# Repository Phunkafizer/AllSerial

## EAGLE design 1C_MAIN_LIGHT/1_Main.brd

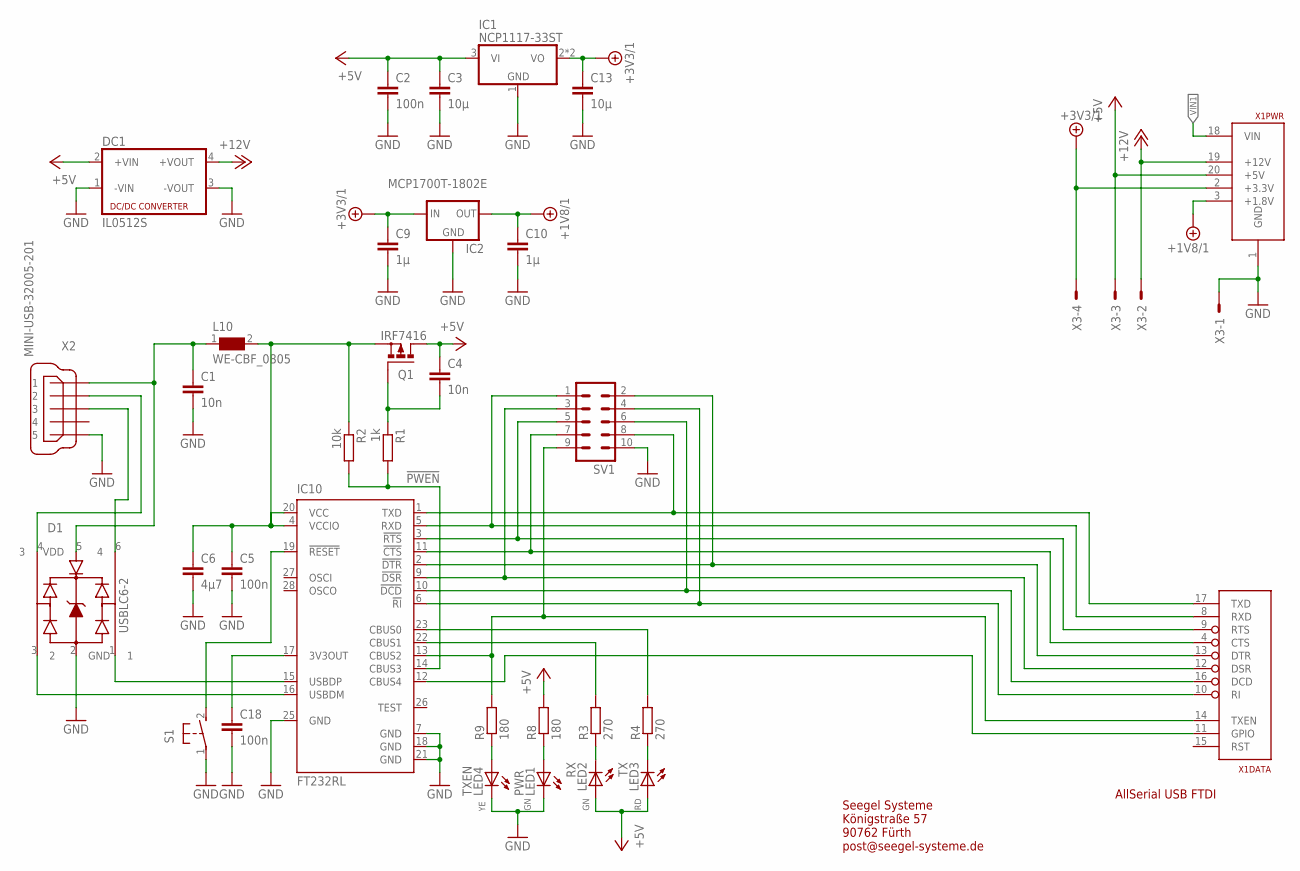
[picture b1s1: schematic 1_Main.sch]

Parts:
C1, C4: 10n; C0805
C2, C5, C18: 100n; C0805
C3, C13: 10µ; C0805
C6: 4µ7; C0805
C9, C10: 1µ; C0805
D1: USBLC6-2; WE-TVS_SOT23-6L
DC1: IL0512S; NME
IC1: NCP1117-33ST; SOT223
IC2: MCP1700T-1802E; SOT23
IC10: FT232RL; SSOP28
L10: WE-CBF_0805; 0805
LED1: PWR; CHIPLED_0603
LED2: RX; CHIPLED_0603
LED3: TX; CHIPLED_0603
LED4: TXEN; CHIPLED_0603
Q1: IRF7416; SO-08
R1: 1k; R0805
R2: 10k; R0805
R3, R4: 270; R0805
R8, R9: 180; R0805
S1: 31-XX; B3F-31XX
SV1: ML10
X1: ALLSERIALMASTERMM; MAIN-THT
X2: MINI-USB-32005-201; 32005-201
X3: AKL18X-04W; AKL182-04

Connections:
!PWEN: IC10.14 (CBUS3), R1.2, R2.2
+1V8/1: C10.1, IC2.2 (OUT), X1.3 (+1.8V)
+3V3/1: C9.1, C13.1, IC1.2 (VO), IC1.4 (VO), IC2.3 (IN), X1.2 (+3.3V), X3.P$4
+5V: C2.1, C3.1, C4.1, DC1.2 (+VIN), IC1.3 (VI), LED2.A, LED3.A, Q1.5 (D), Q1.6 (D), Q1.7 (D), Q1.8 (D), R8.2, X1.20 (+5V), X3.P$3
+12V: DC1.4 (+VOUT), X1.19 (+12V), X3.P$2
GND: C1.2, C2.2, C3.2, C5.2, C6.2, C9.2, C10.2, C13.2, C18.2, D1.2 (GND), DC1.1 (-VIN), DC1.3 (-VOUT), IC1.1 (GND), IC2.1 (GND), IC10.7 (GND), IC10.18 (GND), IC10.21 (GND), IC10.25 (GND), LED1.C, LED4.C, S1.1, SV1.10, X1.1 (GND), X2.5, X3.P$1
unnamed: IC10.5 (RXD), SV1.1, X1.8 (RXD)
unnamed: IC10.9 (!DSR), SV1.3, X1.12 (DSR)
unnamed: IC10.13 (CBUS2), R9.2, SV1.9, X1.14 (TXEN)
unnamed: LED3.C, R4.1
unnamed: IC10.19 (!RESET), S1.2 (S)
unnamed: LED2.C, R3.1
unnamed: LED4.A, R9.1
unnamed: LED1.A, R8.1
unnamed: D1.3 (2), IC10.16 (USBDM)
unnamed: D1.1, IC10.15 (USBDP)
unnamed: C1.1, D1.5 (VDD), L10.1, X2.1
unnamed: D1.4 (3), X2.2
unnamed: IC10.12 (CBUS4), X1.11 (GPIO)
unnamed: IC10.1 (TXD), SV1.8, X1.17 (TXD)
unnamed: D1.6 (4), X2.3
unnamed: C18.1, IC10.17 (3V3OUT)
unnamed: IC10.3 (!RTS), SV1.5, X1.9 (RTS)
unnamed: IC10.11 (!CTS), SV1.7, X1.4 (CTS)
unnamed: IC10.2 (!DTR), SV1.2, X1.13 (DTR)
unnamed: IC10.10 (!DCD), SV1.6, X1.16 (DCD)
unnamed: IC10.6 (!RI), SV1.4, X1.10 (RI)
unnamed: C5.1, C6.1, IC10.4 (VCCIO), IC10.20 (VCC), L10.2, Q1.1 (S), Q1.2 (S), Q1.3 (S), R2.1
unnamed: C4.2, Q1.4 (G), R1.1
RXLED: IC10.22 (CBUS1), R3.2
TXLED: IC10.23 (CBUS0), R4.2
VIN1: X1.18 (VIN)

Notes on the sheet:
AllSerial USB FTDI
Seegel Systeme Königstraße 57 90762 Fürth post@seegel-systeme.de

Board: 2 copper layers, 33 parts (0 on the bottom side), 31 nets, no tracks yet.

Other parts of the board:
U$3: 1296.1004

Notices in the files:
parts and their libraries:
EagleLibrary_Wuerth_Elektronik_eiSos_Ver: Copyright: Würth Elektronik
